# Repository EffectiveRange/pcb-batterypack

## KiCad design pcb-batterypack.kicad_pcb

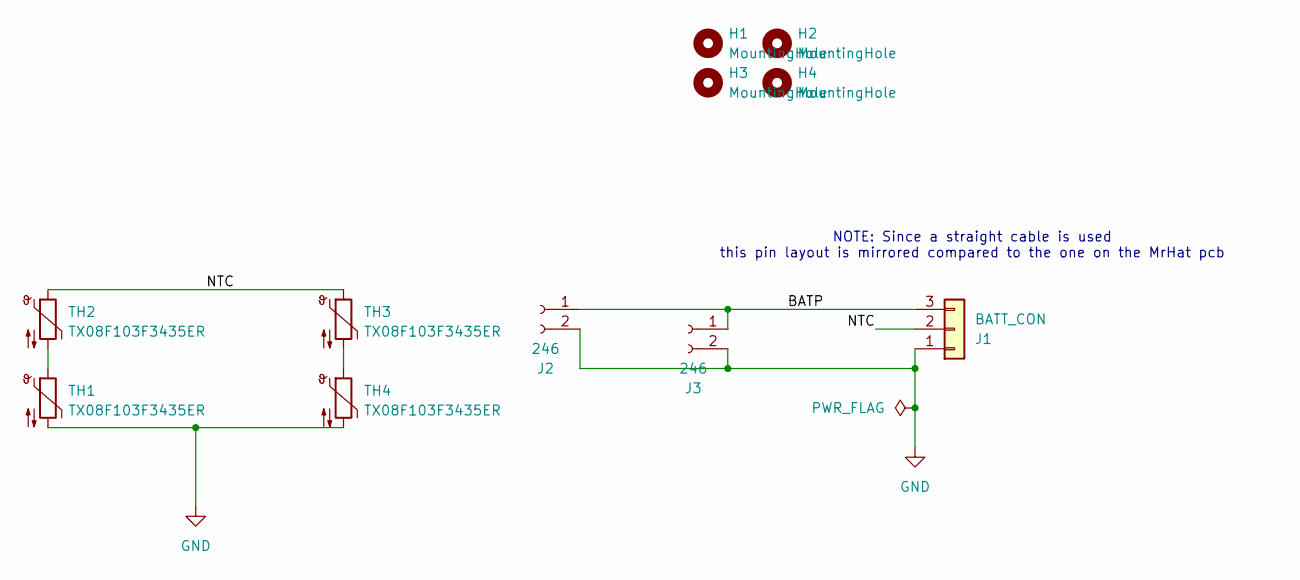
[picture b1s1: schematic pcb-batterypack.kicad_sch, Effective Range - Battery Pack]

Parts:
H1, H2, H3, H4: MountingHole; MountingHole_2.7mm_M2.5
J1: BATT_CON; CONN03_533750310_MOL; MPN 533750310
J2, J3: 246; KeyElco246_cell; MPN 246
TH1, TH2, TH3, TH4: TX08F103F3435ER; R_0805_2012Metric; MPN TX08F103F3435ER

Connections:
/BATP: J1.3, J2.1, J3.1
/NTC: J1.2, TH2.1, TH3.1
GND: J1.1, J2.2, J3.2, TH1.2, TH4.2
unnamed: TH1.1, TH2.2
unnamed: TH3.2, TH4.1

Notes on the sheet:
NOTE: Since a straight cable is used this pin layout is mirrored compared to the one on the MrHat pcb

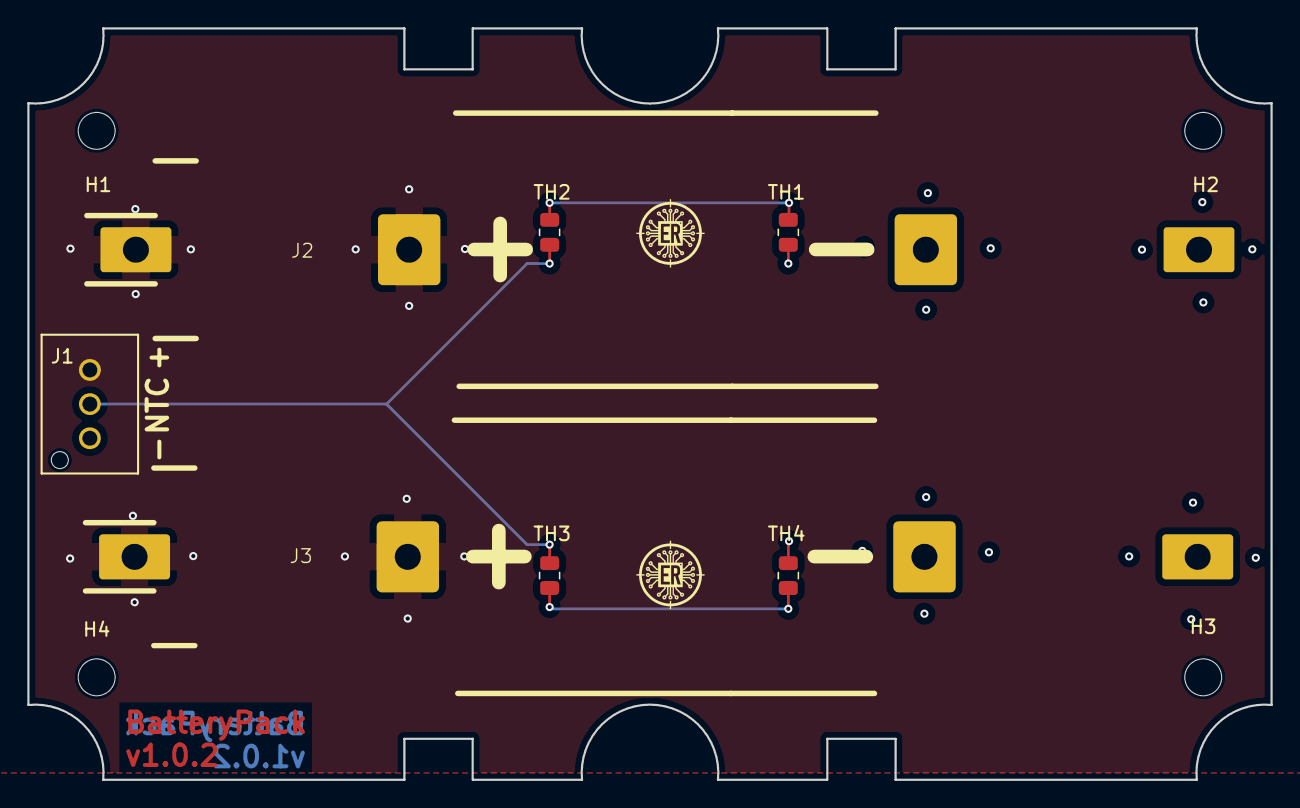
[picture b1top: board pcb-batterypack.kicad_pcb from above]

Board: 4 copper layers, 91.0 x 55.0 mm, 11 parts (0 on the bottom side), 5 nets.

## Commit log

2025-03-02 initial
2025-03-03 initial version
2025-03-03 fixed erc error
2025-03-03 added CI defs
2025-03-03 Bumping release from 1.0.0 to 1.0.0
2025-03-03 fix NTC location and thermal reliefs
2025-03-03 Bumping release from 1.0.0 to 1.0.1
2025-03-03 CI: fix project name extraction
2025-03-03 fix: no via in pad to reduce cost
2025-03-03 Bumping release from 1.0.1 to 1.0.2
2025-06-10 refactor battery pack edge cuts outline
2025-10-15 modified edge cuts geometry
2025-10-15 updated kicad ver
2025-10-15 Bumping release from 1.0.2 to 1.1.0
2026-03-19 fix silkscreen plus minus
2026-03-19 Bumping release from 1.1.0 to 1.1.1

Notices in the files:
pcb-batterypack.kicad_pcb:
visit https://creativecommons.org/licenses/by/4.0
is licensed under CC BY 4.0. To view a copy of this license,
License: MrHAT © 2025 by Ferenc Nandor Janky & Attila Gombos
